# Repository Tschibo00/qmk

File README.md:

This repo contains the QMK files for my keyboards
# qmk

## WARNING
This project is a personal project, i just built one prototype. It's not considered complete, nor tested or error-free.

I won't develop this much, just releasing it as-is for anybody knowledgable picking up and maybe building upon it.

It is NOT ready to take the files and produce a working keyboard!

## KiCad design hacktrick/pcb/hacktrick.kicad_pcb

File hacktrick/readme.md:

# tschibo00/hacktrick

## WARNING
This project is a personal project, i just built one prototype. It's not considered complete, nor tested or error-free.

I won't develop this much, just releasing it as-is for anybody knowledgable picking up and maybe building upon it.

It is NOT ready to take the files and produce a working keyboard!

## What is it?

This was a special project to bring Selectric I keycaps back to life in a MX keyboard.
It required conversion of the keycaps and rotated MX switches (i.e. "sideways").
The keyboard is gasket mounted with a special sound guidance feature to have a more bassy sound.

## hardware
- RPi2040 Zero
- Specifically designed for converted Selectric keycaps

## BOM
- PCB
- Plate
- RPi2040 Zero
- 34 diodes, e.g. 1N4148
- 33 Kailh hot-swap sockets
- 33 key switches of your liking (need simple stem, not box style or round)
- 33 key caps (I use converted Selectric I keycaps)
- Encoder, e.g. Bourns EC11 (I'm using dentless with 24ppr and push)
- 4 heat inserts M2.5 5.7x4.6mm
- 2 screws M2.5x20 (back)
- 2 screws M2.5x16 (front)
- 6 rubber pads 9.5mm diameter
- USB port extension (I used this for looks: https://www.aliexpress.us/item/3256804440339698.html)
- 5x3mm self-adhesive sealing tape for the gasket mount
- bottom case printed
- top case printed
- paint to your likings :)
- optional: 2x220 resistor + 2x LEDs
- optional: dampening (I use cork between PCB+plate and in case bottom)

## Rough build instructions
- Cut out the middle section of the PCB if not already cut out
  - BE AWARE you're cutting fiberglass. PLEASE take appropriate precautions to not risk your health!!!
- Drill a hole in the plate in the middle of the cut out section to accomodate for the encoder (if not yet drilled)
  - BE AWARE you're cutting fiberglass. PLEASE take appropriate precautions to not risk your health!!!
- solder the diodes on top
- solder the hot-swap sockets on bottom
- solder the RPi
- solder short cables (best ribbon) to the encoder. Solder cables to the headers or PCB directly
- carefully put the heat inserts into the case top
- mount USB extension cable and fix it inside the case
- add the sealing tape to the gaskets from all sides
- mount switches and plate
- push encoder through plate hole and tighten screw
- insert PCB sandwich into case top (this has the gasket mount)
- attach USB extension
- carefully close the case (upside down is easier)
- put in and gently tighten the screws

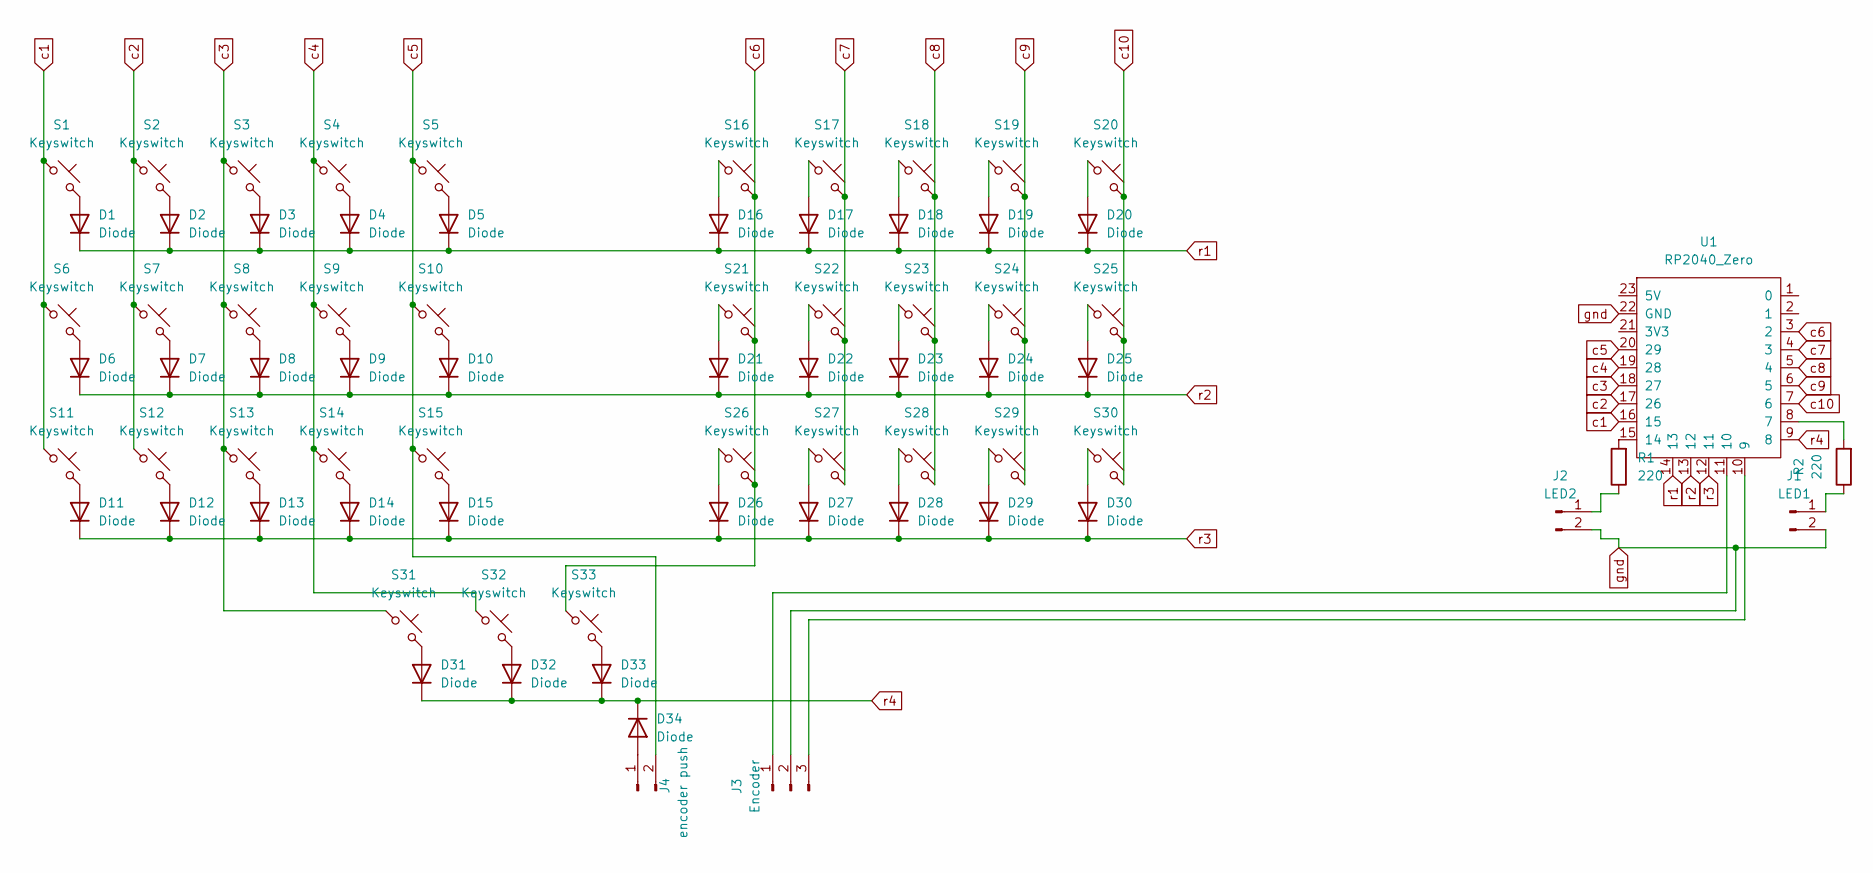
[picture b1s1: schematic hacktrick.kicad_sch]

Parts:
D1, D2, D3, D4, D5, D6, D7, D8, D9, D10, D11, D12, D13, D14, D15, D16, D17, D18, D19, D20, D21, D22, D23, D24, D25, D26, D27, D28, D29, D30, D31, D32, D33, D34: Diode; Diode_DO-35
J1: LED1; PinHeader_1x02_P2.54mm_Vertical
J2: LED2; PinHeader_1x02_P2.54mm_Vertical
J3: Encoder; PinHeader_1x03_P2.54mm_Vertical
J4: encoder push; PinHeader_1x02_P2.54mm_Vertical
R1, R2: 220; R_Axial_DIN0207_L6.3mm_D2.5mm_P7.62mm_Horizontal
S1, S2, S3, S4, S5, S6, S7, S8, S9, S10, S11, S12, S13, S14, S15, S16, S17, S18, S19, S20, S21, S22, S23, S24, S25, S26, S27, S28, S29, S30, S31, S32, S33: Keyswitch; Hotswap_MX_Plated_1.00u
U1: RP2040_Zero

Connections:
unnamed: D1.2 (A), S1.2
unnamed: D2.2 (A), S2.2
unnamed: D3.2 (A), S3.2
unnamed: D4.2 (A), S4.2
unnamed: D5.2 (A), S5.2
unnamed: D6.2 (A), S6.2
unnamed: D7.2 (A), S7.2
unnamed: D8.2 (A), S8.2
unnamed: D9.2 (A), S9.2
unnamed: D10.2 (A), S10.2
unnamed: D11.2 (A), S11.2
unnamed: D12.2 (A), S12.2
unnamed: D13.2 (A), S13.2
unnamed: D14.2 (A), S14.2
unnamed: D15.2 (A), S15.2
unnamed: D16.2 (A), S16.1
unnamed: D17.2 (A), S17.1
unnamed: D18.2 (A), S18.1
unnamed: D19.2 (A), S19.1
unnamed: D20.2 (A), S20.1
unnamed: D21.2 (A), S21.1
unnamed: D22.2 (A), S22.1
unnamed: D23.2 (A), S23.1
unnamed: D24.2 (A), S24.1
unnamed: D25.2 (A), S25.1
unnamed: D26.2 (A), S26.1
unnamed: D27.2 (A), S27.1
unnamed: D28.2 (A), S28.1
unnamed: D29.2 (A), S29.1
unnamed: D30.2 (A), S30.1
unnamed: D31.2 (A), S31.2
unnamed: D32.2 (A), S32.2
unnamed: D33.2 (A), S33.2
unnamed: D34.2 (A), J4.1
unnamed: J1.1, R2.1
unnamed: J2.1, R1.1
unnamed: J3.1, U1.11 (10)
unnamed: J3.3, U1.10 (9)
unnamed: R2.2, U1.8 (7)
unnamed: R1.2, U1.15 (14)
c1: S1.1, S6.1, S11.1, U1.16 (15)
c2: S2.1, S7.1, S12.1, U1.17 (26)
c3: S3.1, S8.1, S13.1, S31.1, U1.18 (27)
c4: S4.1, S9.1, S14.1, S32.1, U1.19 (28)
c5: J4.2, S5.1, S10.1, S15.1, U1.20 (29)
c6: S16.2, S21.2, S26.2, S33.1, U1.3 (2)
c7: S17.2, S22.2, S27.2, U1.4 (3)
c8: S18.2, S23.2, S28.2, U1.5 (4)
c9: S19.2, S24.2, S29.2, U1.6 (5)
c10: S20.2, S25.2, S30.2, U1.7 (6)
gnd: J1.2, J2.2, J3.2, U1.22 (GND)
r1: D1.1 (K), D2.1 (K), D3.1 (K), D4.1 (K), D5.1 (K), D16.1 (K), D17.1 (K), D18.1 (K), D19.1 (K), D20.1 (K), U1.14 (13)
r2: D6.1 (K), D7.1 (K), D8.1 (K), D9.1 (K), D10.1 (K), D21.1 (K), D22.1 (K), D23.1 (K), D24.1 (K), D25.1 (K), U1.13 (12)
r3: D11.1 (K), D12.1 (K), D13.1 (K), D14.1 (K), D15.1 (K), D26.1 (K), D27.1 (K), D28.1 (K), D29.1 (K), D30.1 (K), U1.12 (11)
r4: D31.1 (K), D32.1 (K), D33.1 (K), D34.1 (K), U1.9 (8)

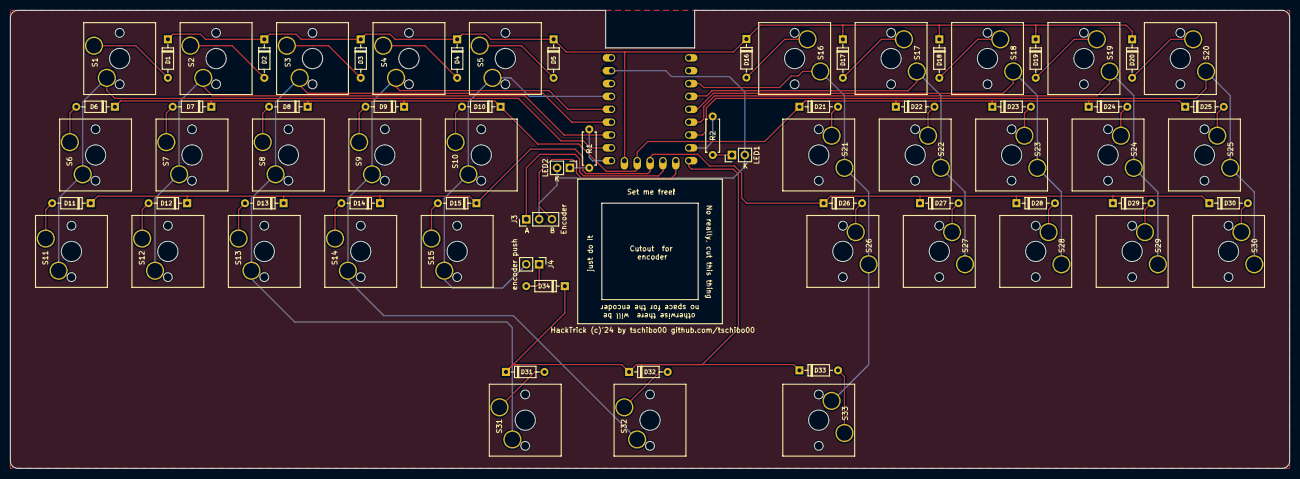
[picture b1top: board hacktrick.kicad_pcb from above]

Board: 2 copper layers, 252.7 x 90.5 mm, 74 parts (0 on the bottom side), 55 nets.

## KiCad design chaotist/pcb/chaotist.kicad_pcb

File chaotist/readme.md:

# tschibo00/chaotist

## WARNING
This project is a personal project, i just built one prototype. It's not considered complete, nor tested or error-free.

I won't develop this much, just releasing it as-is for anybody knowledgable picking up and maybe building upon it.

It is NOT ready to take the files and produce a working keyboard!

## hardware
- RPi2040 Pico
- The current keymaps is designed as either QWERTZ or Colemak DH layout used with US International to have äöüß€ available for combos.
    - however only Colemak is actively developed
- To build the case with the given 3d file, the following additional material is required:
    - M2.5 x 10mm screws and bolts
    - if you want to add the weights, break out the inserts, add 15x2mm metal stripes (e.g. steel) and apply with double-sided tape

## Flashing
Enter the bootloader in 3 ways:

* **Bootmagic reset**: Hold down the key at (0,0) in the matrix (usually the top left key or Escape) and plug in the keyboard
* **Physical reset button**: Briefly press the button on the back of the PCB - some may have pads you must short instead
* **Keycode in layout**: Press the key mapped to `QK_BOOT` if it is available

qmk flash -kb tschibo00/chaotist -km default
qmk flash -kb tschibo00/chaotist -km qwertyFullBottom
qmk flash -kb tschibo00/chaotist -km colemakDhFullBottom

## have a look

## Configurations

```
Regular layout
┌─────┬─────┬─────┬─────┬─────┬─────┬─────┬─────┬─────┬─────┬─────┬─────┐
│0/0  │0/1  │0/2  │0/3  │0/4  │0/5  │0/6  │0/7  │0/8  │0/9  │0/10 │0/11 │
│     │     │     │1u   │     │     │     │     │1u   │     │     │     │
│     │     │1.25u├─────┤1.5u │     │     │1.5u ├─────┤1.25u│     │     │
│     │1.75u├─────┤1/3  ├─────┤1.75u│1.75u├─────┤1/8  ├─────┤1.75u│     │
│     ├─────┤1/2  │1u   │1/4  ├─────┼─────┤1/7  │1u   │1/9  ├─────┤     │
│     │1/1  │1u   ├─────┤1u   │1/5  │1/6  │1u   ├─────┤1u   │1/10 │     │
│2.75u│1u   ├─────┤2/3  ├─────┤1u   │1u   ├─────┤2/8  ├─────┤1u   │2.75u│
├─────┴─────┤2/2  │     │2/4  ├─────┼─────┤2/7  │     │2/9  ├─────┴─────┤
│2/0        │     │     │     │2/5  │2/6  │     │     │     │2/11       │
│2u         │1.5u │1.75u│1.25u│1u   │1u   │1.25u│1.75u│1.5u │2u         │
├────────┬──┴──┬──┴─────┴─────┴─────┴─────┴─────┴─────┴──┬──┴──┬────────┤
│3/0     │3/2  │3/3                                   3/8│3/9  │3/11    │
│1.5u    │1u   │7u                                       │1u   │1.5u    │
└────────┴─────┴─────────────────────────────────────────┴─────┴────────┘
keymap (. are not used points in matrix)
xxxxxxxxxxxx
.xxxxxxxxxx.
x.xxxxxxxx.x
x.xx....xx.x
Alternative layout if more keys are required
┌─────┬─────┬─────┬─────┬─────┬─────┬─────┬─────┬─────┬─────┬─────┬─────┐
│0/0  │0/1  │0/2  │0/3  │0/4  │0/5  │0/6  │0/7  │0/8  │0/9  │0/10 │0/11 │
│     │     │     │     │     │     │     │     │     │     │     │     │
│1.5u │     │1.25u├─────┤1.5u │     │     │1.5u ├─────┤1.25u│     │1.5u │
├─────┤1.75u├─────┤1/3  ├─────┤1.75u│1.75u├─────┤1/8  ├─────┤1.75u├─────┤
│1/0  ├─────┤1/2  │1u   │1/4  ├─────┼─────┤1/7  │1u   │1/9  ├─────┤1/11 │
│     │1/1  │1u   ├─────┤1u   │1/5  │1/6  │1u   ├─────┤1u   │1/10 │     │
│1.25u│1u   ├─────┤2/3  ├─────┤1u   │1u   ├─────┤2/8  ├─────┤1u   │1.25u│
├─────┴─────┤2/2  │     │2/4  ├─────┼─────┤2/7  │     │2/9  ├─────┴─────┤
│2/0        │     │     │     │2/5  │2/6  │     │     │     │2/11       │
│2u         │1.5u │1.75u│1.25u│1u   │1u   │1.25u│1.75u│1.5u │2u         │
├────────┬──┴──┬──┴──┬──┴─────┴──┬──┴──┬──┴─────┴──┬──┴──┬──┴──┬────────┤
│3/0     │3/2  │3/3  │3/4        │3/5  │3/7        │3/8  │3/9  │3/11    │
│1.5u    │1u   │1u   │2u         │1u   │2u         │1u   │1u   │1.5u    │
└────────┴─────┴─────┴───────────┴─────┴───────────┴─────┴─────┴────────┘
keymap (. are not used points in matrix)
xxxxxxxxxxxx
xxxxxxxxxxxx
x.xxxxxxxx.x
x.xxxx.xxx.x
```

# Todos
- [x] correct keyboard matrix in info.json
- [x] use correct del line macro
- [x] add macros from other code
- [x] add colemak dh
- [x] make better use of function layer
- [x] think about utilizing move layer better
- [x] move escape somewhere else to avoid accidental presses
- [x] add case file with build instructions
- [x] move more critical commands like boot to a special layer thats not triggered accidentally
- [-] try to use space/underscore again
- [x] add audio layer
- [x] add repeat on delete
- [x] add missing symbols like percent, angled brackets
- [x] use magic key as leader key and hold for shift
- [x] switch ; and : in base layer (or think of a better way to use the key :D)
- [ ] make layer switch permanent, when combined with leader key. switch back to base layer on next leader key press

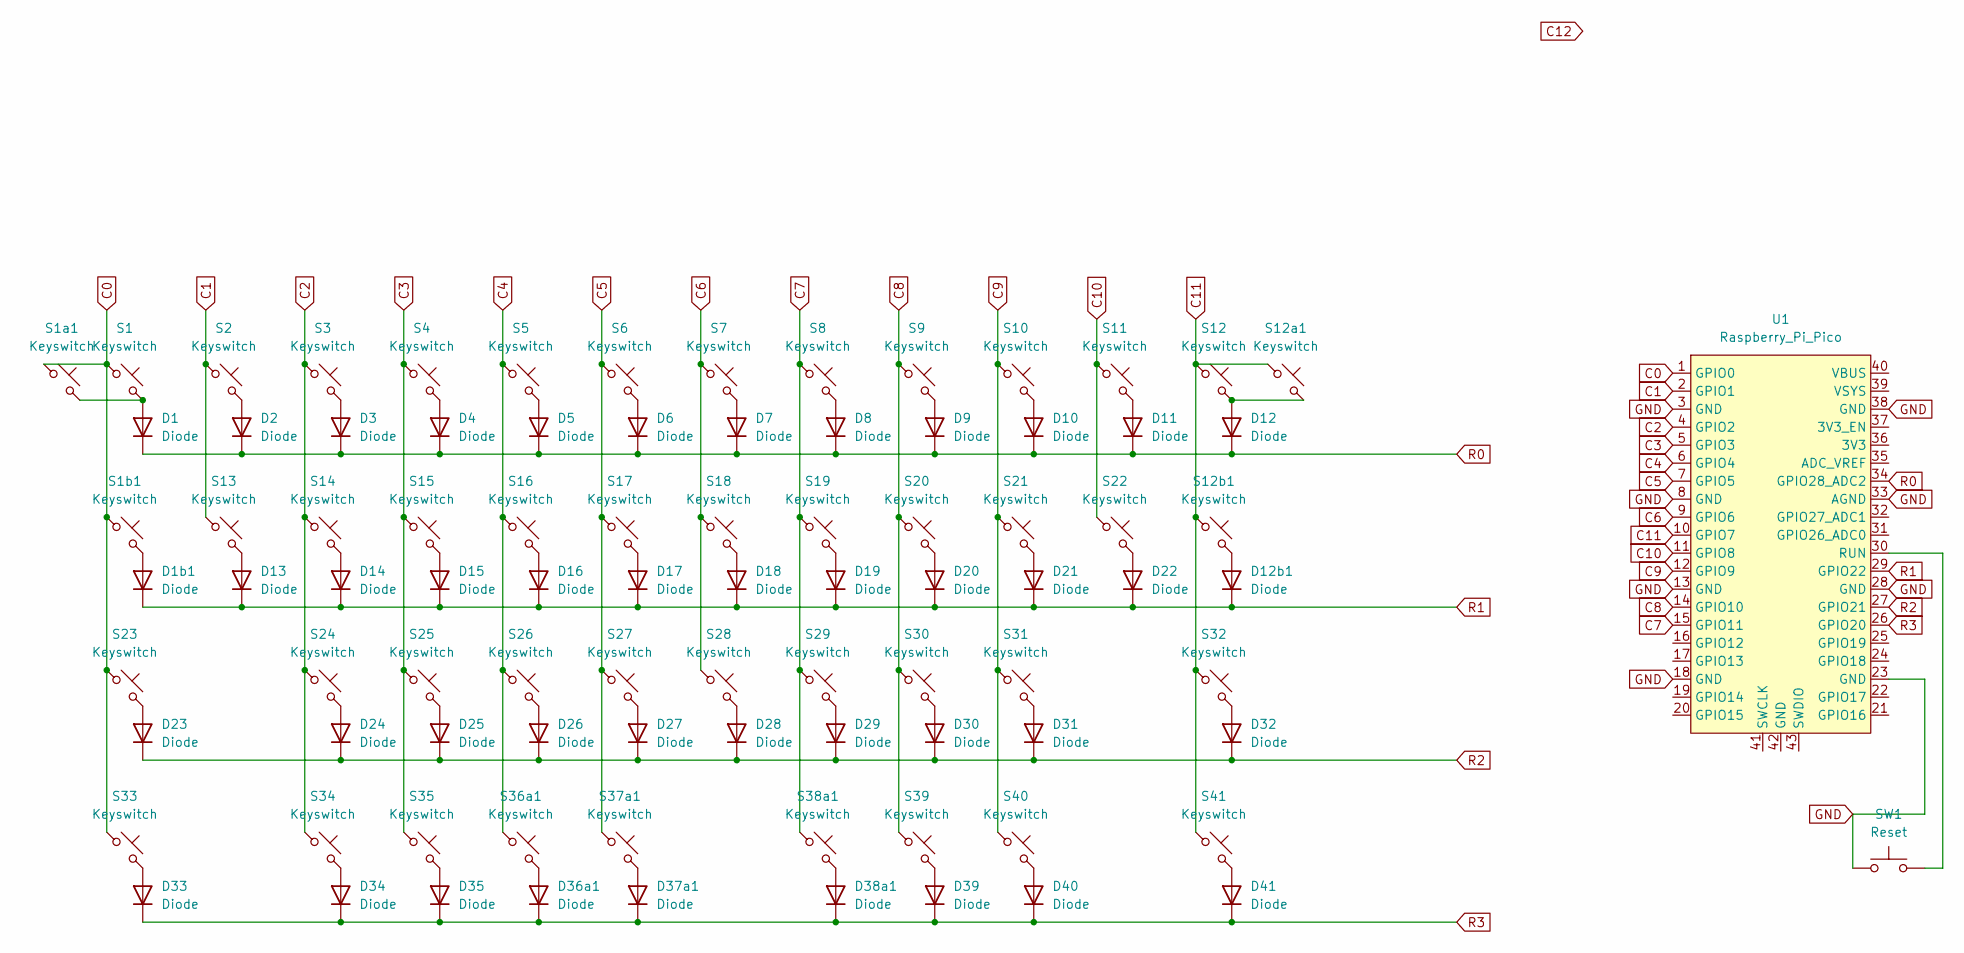
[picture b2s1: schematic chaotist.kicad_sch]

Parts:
D1, D1b1, D2, D3, D4, D5, D6, D7, D8, D9, D10, D11, D12, D12b1, D13, D14, D15, D16, D17, D18, D19, D20, D21, D22, D23, D24, D25, D26, D27, D28, D29, D30, D31, D32, D33, D34, D35, D36a1, D37a1, D38a1, D39, D40, D41: Diode; Diode_DO-35
S1, S12: Keyswitch; MX_PCB_2.75u
S1a1, S12a1: Keyswitch; MX_Plate_1.50u
S1b1, S12b1: Keyswitch; MX_Plate_1.25u
S2, S6, S7, S11, S25, S30: Keyswitch; MX_PCB_1.75u
S3, S10, S26, S29: Keyswitch; MX_PCB_1.25u
S4, S9, S13, S14, S15, S16, S17, S18, S19, S20, S21, S22, S27, S28, S34, S35, S37a1, S39, S40: Keyswitch; MX_PCB_1.00u
S5, S8, S24, S31, S33, S41: Keyswitch; MX_PCB_1.50u
S23, S32, S36a1, S38a1: Keyswitch; MX_PCB_2.00u
SW1: Reset; SW_PUSH_6mm_H4.3mm
U1: Raspberry_Pi_Pico

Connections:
C0: S1.1, S1a1.1, S1b1.1, S23.1, S33.1, U1.1 (GPIO0)
C1: S2.1, S13.1, U1.2 (GPIO1)
C2: S3.1, S14.1, S24.1, S34.1, U1.4 (GPIO2)
C3: S4.1, S15.1, S25.1, S35.1, U1.5 (GPIO3)
C4: S5.1, S16.1, S26.1, S36a1.1, U1.6 (GPIO4)
C5: S6.1, S17.1, S27.1, S37a1.1, U1.7 (GPIO5)
C6: S7.1, S18.1, S28.1, U1.9 (GPIO6)
C7: S8.1, S19.1, S29.1, S38a1.1, U1.15 (GPIO11)
C8: S9.1, S20.1, S30.1, S39.1, U1.14 (GPIO10)
C9: S10.1, S21.1, S31.1, S40.1, U1.12 (GPIO9)
C10: S11.1, S22.1, U1.11 (GPIO8)
C11: S12.1, S12a1.1, S12b1.1, S32.1, S41.1, U1.10 (GPIO7)
GND: SW1.1, U1.3 (GND), U1.8 (GND), U1.13 (GND), U1.18 (GND), U1.23 (GND), U1.28 (GND), U1.33 (AGND), U1.38 (GND)
unnamed: D1.2 (A), S1.2, S1a1.2
unnamed: D1b1.2 (A), S1b1.2
unnamed: D2.2 (A), S2.2
unnamed: D3.2 (A), S3.2
unnamed: D4.2 (A), S4.2
unnamed: D5.2 (A), S5.2
unnamed: D6.2 (A), S6.2
unnamed: D7.2 (A), S7.2
unnamed: D8.2 (A), S8.2
unnamed: D9.2 (A), S9.2
unnamed: D10.2 (A), S10.2
unnamed: D11.2 (A), S11.2
unnamed: D12.2 (A), S12.2, S12a1.2
unnamed: D12b1.2 (A), S12b1.2
unnamed: D13.2 (A), S13.2
unnamed: D14.2 (A), S14.2
unnamed: D15.2 (A), S15.2
unnamed: D16.2 (A), S16.2
unnamed: D17.2 (A), S17.2
unnamed: D18.2 (A), S18.2
unnamed: D19.2 (A), S19.2
unnamed: D20.2 (A), S20.2
unnamed: D21.2 (A), S21.2
unnamed: D22.2 (A), S22.2
unnamed: D23.2 (A), S23.2
unnamed: D24.2 (A), S24.2
unnamed: D25.2 (A), S25.2
unnamed: D26.2 (A), S26.2
unnamed: D27.2 (A), S27.2
unnamed: D28.2 (A), S28.2
unnamed: D29.2 (A), S29.2
unnamed: D30.2 (A), S30.2
unnamed: D31.2 (A), S31.2
unnamed: D32.2 (A), S32.2
unnamed: D33.2 (A), S33.2
unnamed: D34.2 (A), S34.2
unnamed: D35.2 (A), S35.2
unnamed: D36a1.2 (A), S36a1.2
unnamed: D37a1.2 (A), S37a1.2
unnamed: D38a1.2 (A), S38a1.2
unnamed: D39.2 (A), S39.2
unnamed: D40.2 (A), S40.2
unnamed: D41.2 (A), S41.2
unnamed: SW1.2, U1.30 (RUN)
R0: D1.1 (K), D2.1 (K), D3.1 (K), D4.1 (K), D5.1 (K), D6.1 (K), D7.1 (K), D8.1 (K), D9.1 (K), D10.1 (K), D11.1 (K), D12.1 (K), U1.34 (GPIO28_ADC2)
R1: D1b1.1 (K), D12b1.1 (K), D13.1 (K), D14.1 (K), D15.1 (K), D16.1 (K), D17.1 (K), D18.1 (K), D19.1 (K), D20.1 (K), D21.1 (K), D22.1 (K), U1.29 (GPIO22)
R2: D23.1 (K), D24.1 (K), D25.1 (K), D26.1 (K), D27.1 (K), D28.1 (K), D29.1 (K), D30.1 (K), D31.1 (K), D32.1 (K), U1.27 (GPIO21)
R3: D33.1 (K), D34.1 (K), D35.1 (K), D36a1.1 (K), D37a1.1 (K), D38a1.1 (K), D39.1 (K), D40.1 (K), D41.1 (K), U1.26 (GPIO20)

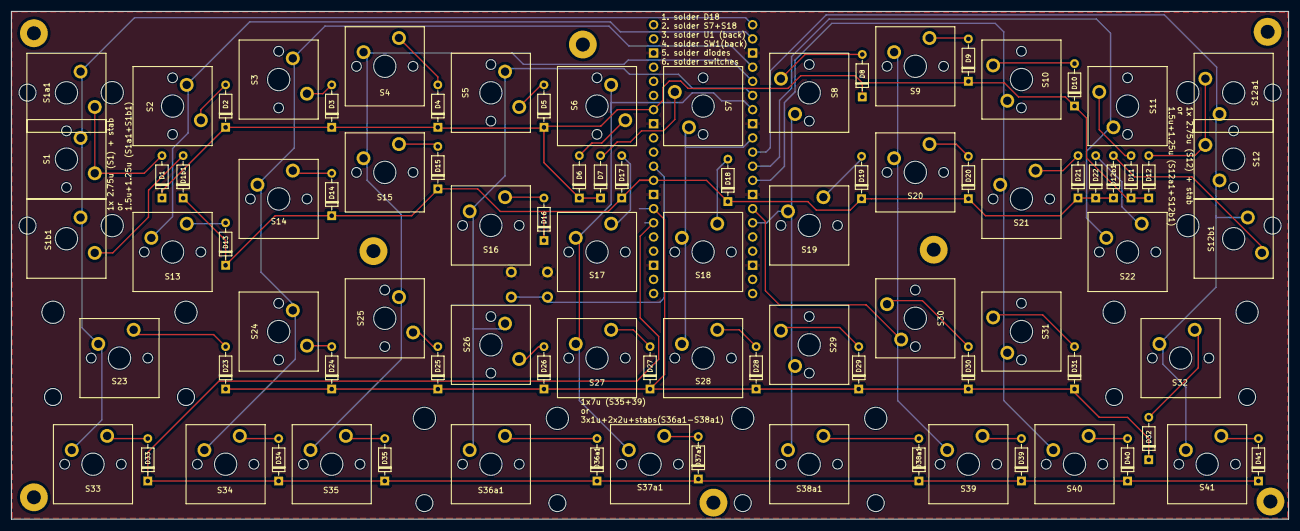
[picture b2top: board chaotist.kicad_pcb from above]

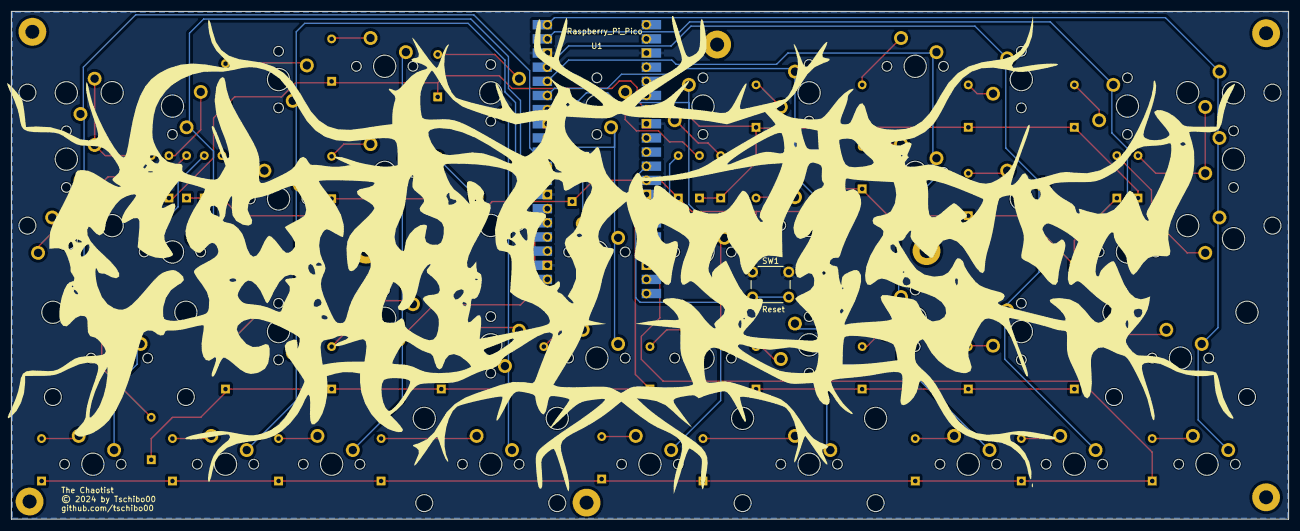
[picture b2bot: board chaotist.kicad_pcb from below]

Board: 2 copper layers, 229.3 x 91.2 mm, 90 parts (2 on the bottom side), 61 nets.

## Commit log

2023-11-18 Add files via upload
    added more layers, only rudimentary.
    Things still missing and autoshift to short
    Plus iso vs. Ansi is killing me
2023-11-19 Add files via upload
    added remaining layers
2023-11-19 Add files via upload
    corrected wrong modifier usage
2023-11-19 Add files via upload
    corrected wrong layers
2023-11-19 Add files via upload
    fixed umlauts
2024-01-22 init
2024-01-25 Add files via upload
    initial upload
2024-01-25 Add files via upload
    fixed left bottom ctrl; cleanup
2024-01-26 fixed oom
2024-01-26 cleanup
2024-01-30 updated pcb; added initial code
2024-01-30 final version for production
2024-02-09 first partially usable keymap
2024-02-10 reduced stagger on pinky, fixed overall layout
2024-02-10 fixed linebreak
2024-02-10 current layout
2024-02-11 corrected 0 key
2024-02-12 Create LICENSE
2024-02-12 Update LICENSE from Apache 2.0 to MIT
2024-02-18 added magic layer; reworked function layer;optimization
2024-02-18 initial case
2024-03-02 added additional keymap for fully populated bottom row
2024-03-16 added colemak with extra layers
2024-03-16 added case file
2024-03-23 fixed format; added leader key stuff
2024-03-23 reworked magic/leader keys
2024-03-23 removed deprecated layout example
2024-03-23 fixed missing keys, uncomfortable stuff
2024-03-23 format
2024-03-25 reworked layout
2024-04-14 initial upload
2024-04-21 reworked lots of stuff, aligned with ToKeyO keymap
2024-04-22 fine tuned thumb cluster
2024-04-22 even more fine tuning
2024-05-10 corrected keymap.c (plus spacing of code)
2024-05-31 fixed indent to spaces
2024-05-31 added "select line"
2024-10-17 Add files via upload
    removed most combos, make more use of one-shot key
2024-10-17 Update keymap.c
    corrected comments
2024-10-18 Add files via upload
    corrections
2024-10-18 Add files via upload
    added homerow mods; corrections
2024-11-08 use BRMs instead of thumb keys. get rid of middle thumb keys
2025-01-13 added BOM
2025-01-13 added build instructions
2025-01-13 corrected ascii layout of comments
2025-01-14 Corrected screws and added switch hint
2025-01-17 added del+bksp on left side
2025-03-10 added lt/gt, fixed some mappings to more reasonable place
2025-09-09 removing stray wire
2025-09-11 initial
2025-09-11 correct encoder assignment
2025-10-09 added missing G key connection for Chocs
2025-10-27 fix old settings

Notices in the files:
chaotist/pcb/chaotist.kicad_pcb:
© 2024 by Tschibo00
